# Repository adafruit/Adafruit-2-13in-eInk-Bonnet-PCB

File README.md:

## Adafruit 2.13" Monochrome eInk Bonnet for Raspberry Pi PCB

<a href="http://www.adafruit.com/products/4687"><br/>
Click here to purchase one from the Adafruit shop</a>

PCB files for the Adafruit 2.13" Monochrome eInk Bonnet for Raspberry Pi.

Format is EagleCAD schematic and board layout
* https://www.adafruit.com/product/4687

### Description

Easy e-paper finally comes to Raspberry Pi, with this bonnet that's designed to make it a breeze to add a 2.13" 250x122 crisp monochromic eInk display. Chances are you've seen one of those new-fangled 'e-readers' like the Kindle or Nook. They have gigantic electronic paper 'static' displays - that means the image stays on the display even when power is completely disconnected. The image is also high contrast and very daylight readable. It really does look just like printed paper!

The Adafruit 2.13" Monochrome E-Ink Bonnet for Raspberry Pi snaps onto any modern Raspberry Pi and provides a Python-programmable display with two buttons that can be used to select programs or scroll through options.

We have two fun starter guides to use with this bonnet, an Open Weather display and an event calendar that auto-syncs with a Google Calendar to show you what your next meeting or event is. We also have examples in our E-Ink Python library you can use to craft your own project

Comes completely pre-assembled and tested so you don't need to do anything but plug it in and install our Python code! Works with any Raspberry Pi computer that has a 2x20 connector, such as the Pi B+, Pi 2, Pi 3, Pi 4, and Pi Zero (and any others that have a 2x20 connector!)

On the bottom, we have a Qwiic/STEMMA QT connector for I2C sensors and devices so you can plug and play any of our STEMMA QT devices.

### License

Adafruit invests time and resources providing this open source design, please support Adafruit and open-source hardware by purchasing products from [Adafruit](https://www.adafruit.com)!

Designed by Limor Fried/Ladyada for Adafruit Industries.

Creative Commons Attribution/Share-Alike, all text above must be included in any redistribution.
See license.txt for additional details.

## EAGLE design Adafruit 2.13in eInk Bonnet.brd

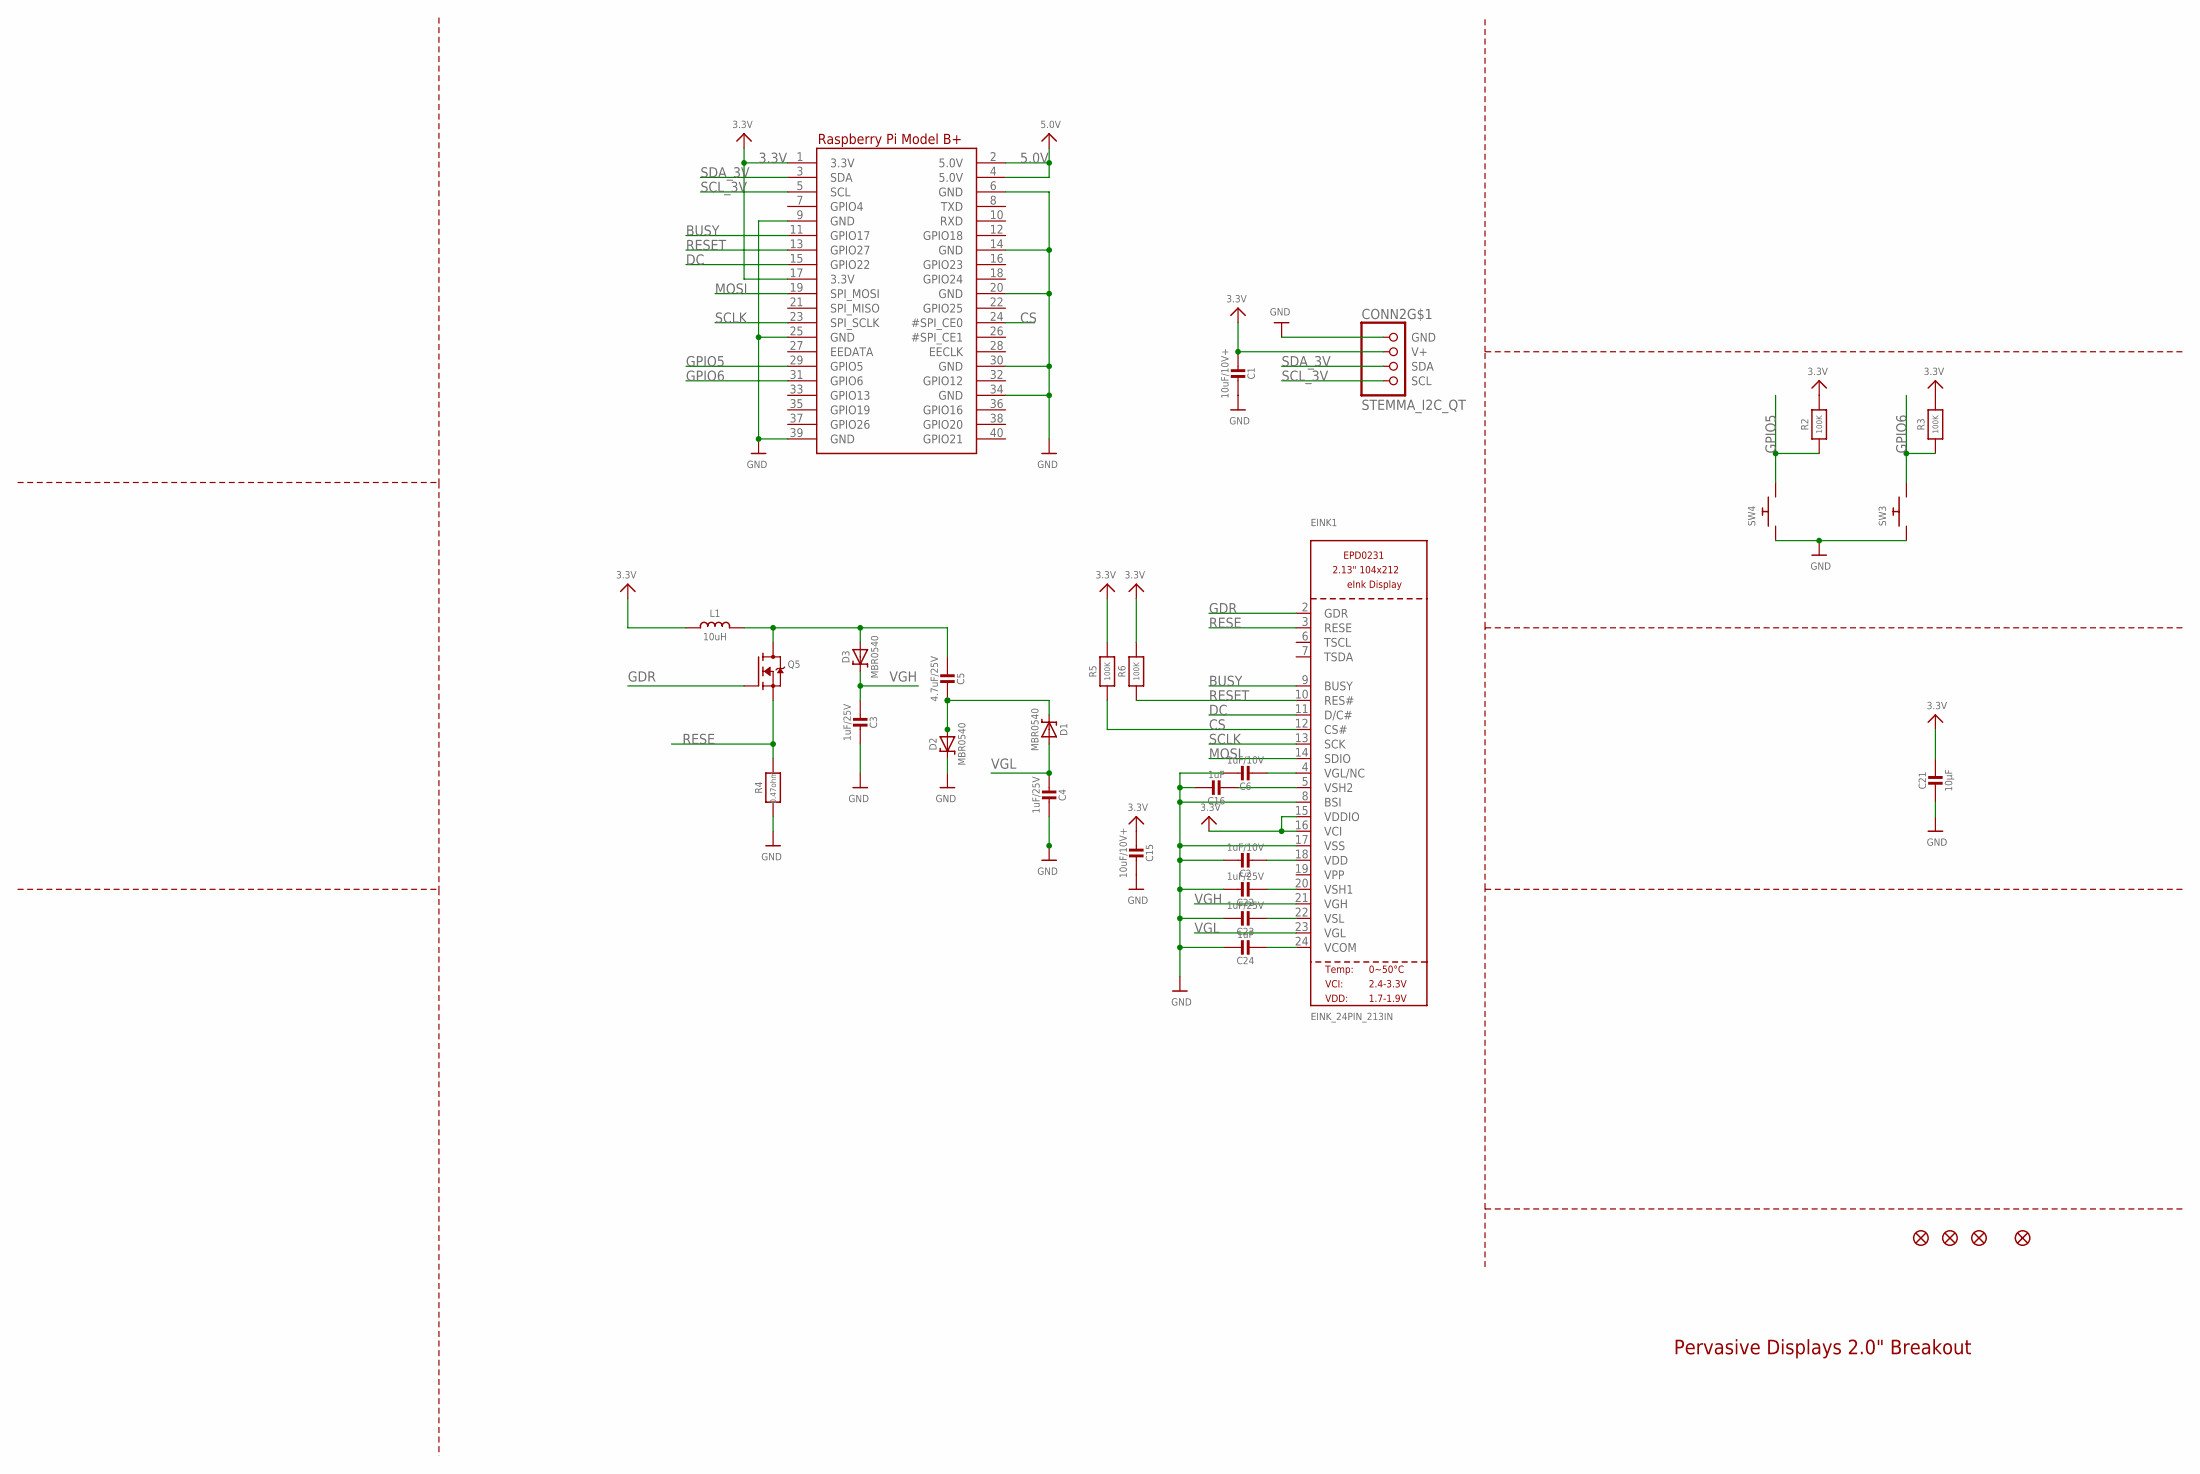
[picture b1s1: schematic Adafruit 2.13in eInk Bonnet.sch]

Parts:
C1, C15: 10uF/10V+; 0805-NO
C2, C6: 1uF/10V; 0805-NO
C3, C4, C22, C23: 1uF/25V; 0805-NO
C5: 4.7uF/25V; 0805-NO
C16, C24: 1uF; 0805-NO
C21: 10µF; 0805-NO
CONN2: STEMMA_I2C_QT; JST_SH4
D1, D2, D3: MBR0540; SOD-123
EINK1: EINK_24PIN_213IN; EINK_213IN_104X212
FID1, FID2, FID3, FID4: FIDUCIAL_1MM
L1: 10uH; INDUCTOR_4X4MM_NR401
Q5: IRLML0100; SOT23-3
R2, R3, R5, R6: 100K; 0603-NO
R4: 0.47ohm; 0805_10MGAP
RPI2: RASPBERRYPI_BPLUS_SMT_NODIM; PI_BONNET_SMT_NODIM
SW3, SW4: SWITCH_PUSHBUTTON_3.5X6MM; TACTILE_3X6MM

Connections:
3.3V: C1.2, C15.2, C21.1, CONN2.2 (V+), EINK1.15 (VDDIO), EINK1.16 (VCI), L1.P$2 (2), R2.2, R3.2, R5.2, R6.2, RPI2.1 (3.3V), RPI2.17 (3.3V)
5.0V: RPI2.2 (5.0V), RPI2.4 (5.0V)
BUSY: EINK1.9 (BUSY), RPI2.11 (GPIO17)
CS: EINK1.12 (CS#), R5.1, RPI2.24 (#SPI_CE0)
DC: EINK1.11 (D/C#), RPI2.15 (GPIO22)
GDR: EINK1.2 (GDR), Q5.1 (G)
GND: C1.1, C2.1, C3.2, C4.2, C6.1, C15.1, C16.1, C21.2, C22.1, C23.1, C24.1, CONN2.1 (GND), D2.C, EINK1.8 (BSI), EINK1.17 (VSS), R4.2, RPI2.6 (GND), RPI2.9 (GND), RPI2.14 (GND), RPI2.20 (GND), RPI2.25 (GND), RPI2.30 (GND), RPI2.34 (GND), RPI2.39 (GND), SW3.P$1, SW4.P$1
GPIO5: R2.1, RPI2.29 (GPIO5), SW4.P$2
GPIO6: R3.1, RPI2.31 (GPIO6), SW3.P$2
MOSI: EINK1.14 (SDIO), RPI2.19 (SPI_MOSI)
unnamed: C5.2, D1.C, D2.A
unnamed: C5.1, D3.A, L1.P$1 (1), Q5.3 (D)
unnamed: C16.2, EINK1.5 (VSH2)
unnamed: C2.2, EINK1.18 (VDD)
unnamed: C22.2, EINK1.20 (VSH1)
unnamed: C6.2, EINK1.4 (VGL/NC)
unnamed: C23.2, EINK1.22 (VSL)
unnamed: C24.2, EINK1.24 (VCOM)
RESE: EINK1.3 (RESE), Q5.2 (S), R4.1
RESET: EINK1.10 (RES#), R6.1, RPI2.13 (GPIO27)
SCLK: EINK1.13 (SCK), RPI2.23 (SPI_SCLK)
SCL_3V: CONN2.4 (SCL), RPI2.5 (SCL)
SDA_3V: CONN2.3 (SDA), RPI2.3 (SDA)
VGH: C3.1, D3.C, EINK1.21 (VGH)
VGL: C4.1, D1.A, EINK1.23 (VGL)

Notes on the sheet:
Pervasive Displays 2.0" Breakout

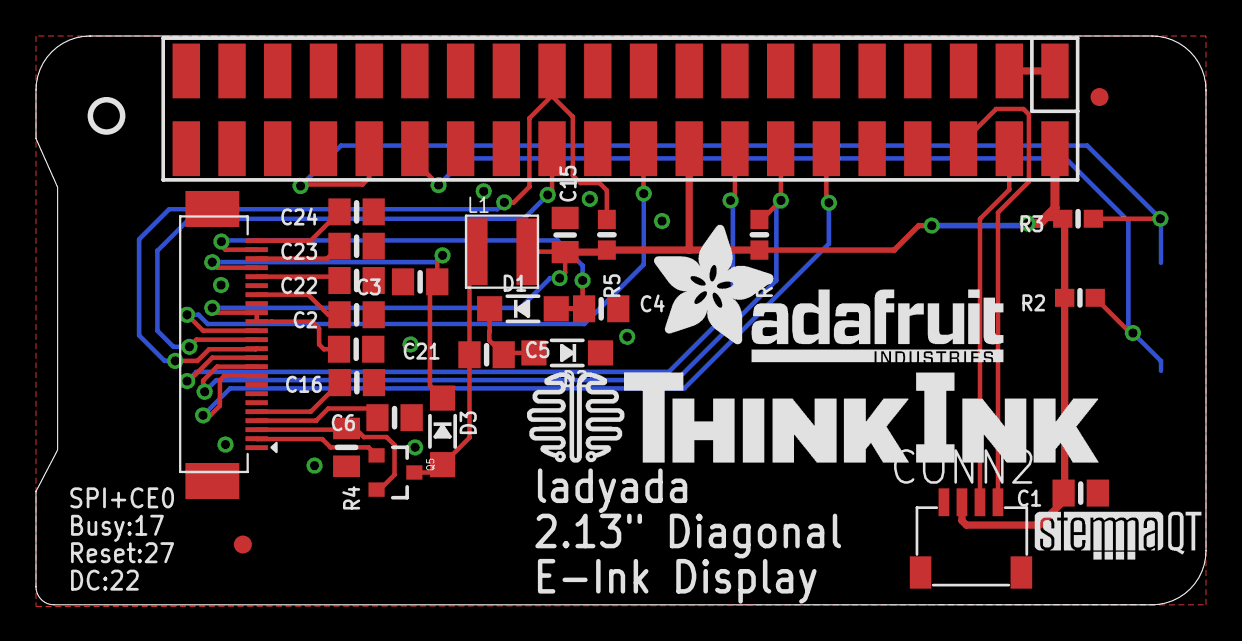
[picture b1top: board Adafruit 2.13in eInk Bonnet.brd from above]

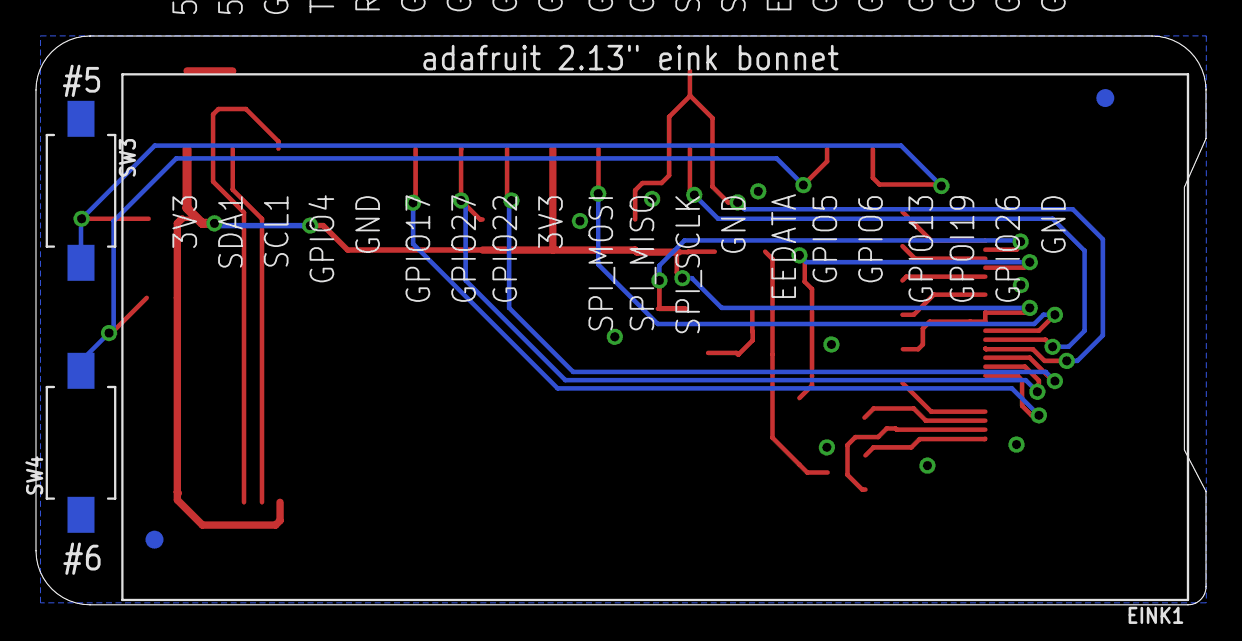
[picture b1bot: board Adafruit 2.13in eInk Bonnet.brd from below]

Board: 2 copper layers, 65.0 x 31.6 mm, 35 parts (6 on the bottom side), 25 nets.

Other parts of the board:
U$9: PCBFEAT-REV-040
U$28: ADAFRUIT_TEXT_20MM
U$29: THINKINK_1.25IN
U$30: STEMMAQT

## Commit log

2020-08-13 Adding board files.

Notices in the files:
parts and their libraries:
microbuilder: This work is placed in the public domain, and may be freely used for commercial and non-commercial work with the following conditions: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
